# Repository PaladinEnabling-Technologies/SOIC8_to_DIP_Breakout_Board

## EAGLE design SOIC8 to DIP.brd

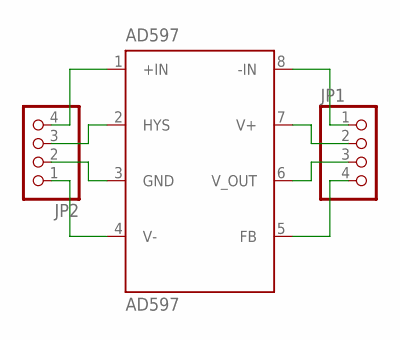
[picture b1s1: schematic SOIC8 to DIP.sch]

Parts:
AD597: AD597; SO8
JP1, JP2: PINHD-1X4; 1X04

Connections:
unnamed: AD597.1 (+IN), JP2.4
unnamed: AD597.2 (HYS), JP2.3
unnamed: AD597.3 (GND), JP2.2
unnamed: AD597.4 (V-), JP2.1
unnamed: AD597.6 (V_OUT), JP1.3
unnamed: AD597.7 (V+), JP1.2
unnamed: AD597.8 (-IN), JP1.1
unnamed: AD597.5 (FB), JP1.4

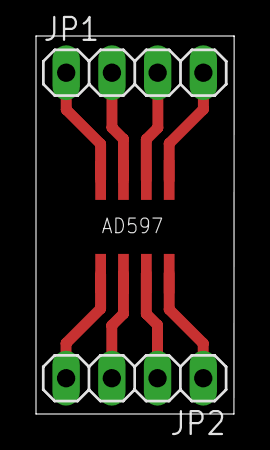
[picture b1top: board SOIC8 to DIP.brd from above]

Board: 2 copper layers, 11.0 x 21.0 mm, 3 parts (0 on the bottom side), 8 nets.

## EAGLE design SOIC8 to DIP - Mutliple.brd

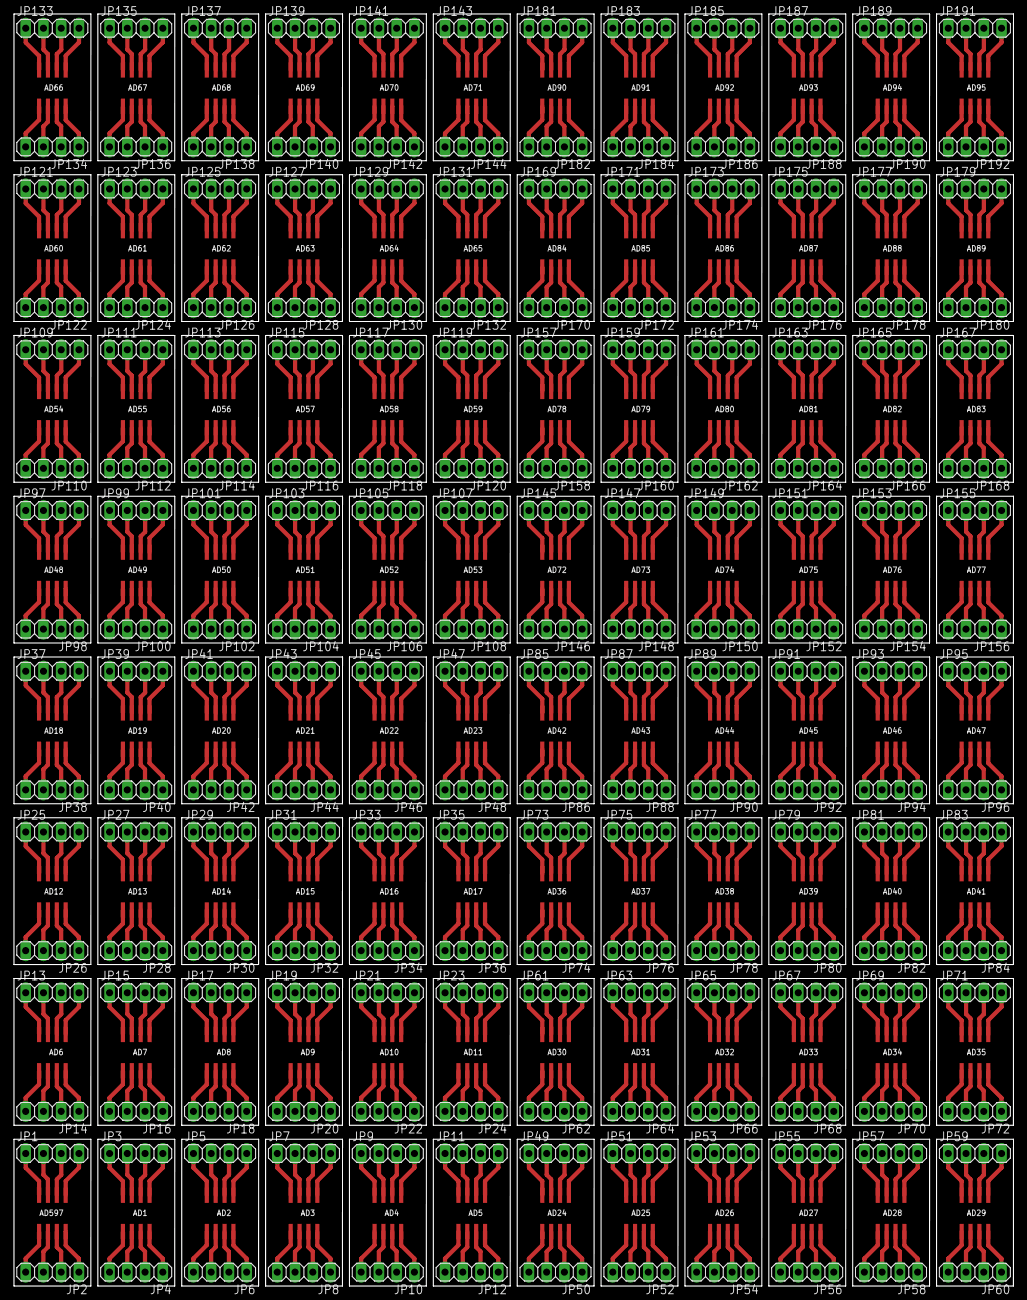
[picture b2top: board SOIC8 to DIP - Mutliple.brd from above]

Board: 2 copper layers, 143.0 x 182.0 mm, 288 parts (0 on the bottom side), 768 nets.

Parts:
AD1, AD2, AD3, AD4, AD5, AD6, AD7, AD8, AD9, AD10, AD11, AD12, AD13, AD14, AD15, AD16, AD17, AD18, AD19, AD20, AD21, AD22, AD23, AD24, AD25, AD26, AD27, AD28, AD29, AD30, AD31, AD32, AD33, AD34, AD35, AD36, AD37, AD38, AD39, AD40, AD41, AD42, AD43, AD44, AD45, AD46, AD47, AD48, AD49, AD50, AD51, AD52, AD53, AD54, AD55, AD56, AD57, AD58, AD59, AD60, AD61, AD62, AD63, AD64, AD65, AD66, AD67, AD68, AD69, AD70, AD71, AD72, AD73, AD74, AD75, AD76, AD77, AD78, AD79, AD80, AD81, AD82, AD83, AD84, AD85, AD86, AD87, AD88, AD89, AD90, AD91, AD92, AD93, AD94, AD95, AD597: AD597; SO8
JP1, JP2, JP3, JP4, JP5, JP6, JP7, JP8, JP9, JP10, JP11, JP12, JP13, JP14, JP15, JP16, JP17, JP18, JP19, JP20, JP21, JP22, JP23, JP24, JP25, JP26, JP27, JP28, JP29, JP30, JP31, JP32, JP33, JP34, JP35, JP36, JP37, JP38, JP39, JP40, JP41, JP42, JP43, JP44, JP45, JP46, JP47, JP48, JP49, JP50, JP51, JP52, JP53, JP54, JP55, JP56, JP57, JP58, JP59, JP60, JP61, JP62, JP63, JP64, JP65, JP66, JP67, JP68, JP69, JP70, JP71, JP72, JP73, JP74, JP75, JP76, JP77, JP78, JP79, JP80, JP81, JP82, JP83, JP84, JP85, JP86, JP87, JP88, JP89, JP90, JP91, JP92, JP93, JP94, JP95, JP96, JP97, JP98, JP99, JP100, JP101, JP102, JP103, JP104, JP105, JP106, JP107, JP108, JP109, JP110, JP111, JP112, JP113, JP114, JP115, JP116, JP117, JP118, JP119, JP120, JP121, JP122, JP123, JP124, JP125, JP126, JP127, JP128, JP129, JP130, JP131, JP132, JP133, JP134, JP135, JP136, JP137, JP138, JP139, JP140, JP141, JP142, JP143, JP144, JP145, JP146, JP147, JP148, JP149, JP150, JP151, JP152, JP153, JP154, JP155, JP156, JP157, JP158, JP159, JP160, JP161, JP162, JP163, JP164, JP165, JP166, JP167, JP168, JP169, JP170, JP171, JP172, JP173, JP174, JP175, JP176, JP177, JP178, JP179, JP180, JP181, JP182, JP183, JP184, JP185, JP186, JP187, JP188, JP189, JP190, JP191, JP192: 1X04

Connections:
unnamed: AD597.1, JP2.4
unnamed: AD1.1, JP4.4
unnamed: AD597.2, JP2.3
unnamed: AD597.3, JP2.2
unnamed: AD597.4, JP2.1
unnamed: AD1.2, JP4.3
unnamed: AD597.6, JP1.3
unnamed: AD1.3, JP4.2
unnamed: AD1.4, JP4.1
unnamed: AD1.6, JP3.3
unnamed: AD597.7, JP1.2
unnamed: AD597.8, JP1.1
unnamed: AD597.5, JP1.4
unnamed: AD1.7, JP3.2
unnamed: AD1.8, JP3.1
unnamed: AD1.5, JP3.4
unnamed: AD2.1, JP6.4
unnamed: AD2.2, JP6.3
unnamed: AD2.3, JP6.2
unnamed: AD2.4, JP6.1
unnamed: AD2.6, JP5.3
unnamed: AD2.7, JP5.2
unnamed: AD2.8, JP5.1
unnamed: AD2.5, JP5.4
unnamed: AD3.1, JP8.4
unnamed: AD3.2, JP8.3
unnamed: AD3.3, JP8.2
unnamed: AD3.4, JP8.1
unnamed: AD3.6, JP7.3
unnamed: AD3.7, JP7.2
unnamed: AD3.8, JP7.1
unnamed: AD3.5, JP7.4
unnamed: AD4.1, JP10.4
unnamed: AD4.2, JP10.3
unnamed: AD4.3, JP10.2
unnamed: AD4.4, JP10.1
unnamed: AD4.6, JP9.3
unnamed: AD4.7, JP9.2
unnamed: AD4.8, JP9.1
unnamed: AD4.5, JP9.4
unnamed: AD5.1, JP12.4
unnamed: AD5.2, JP12.3
unnamed: AD5.3, JP12.2
unnamed: AD5.4, JP12.1
unnamed: AD5.6, JP11.3
unnamed: AD5.7, JP11.2
unnamed: AD5.8, JP11.1
unnamed: AD5.5, JP11.4
unnamed: AD6.1, JP14.4
unnamed: AD6.2, JP14.3
unnamed: AD6.3, JP14.2
unnamed: AD6.4, JP14.1
unnamed: AD6.6, JP13.3
unnamed: AD6.7, JP13.2
unnamed: AD6.8, JP13.1
unnamed: AD6.5, JP13.4
unnamed: AD7.1, JP16.4
unnamed: AD7.2, JP16.3
unnamed: AD7.3, JP16.2
unnamed: AD7.4, JP16.1
unnamed: AD7.6, JP15.3
unnamed: AD7.7, JP15.2
unnamed: AD7.8, JP15.1
unnamed: AD7.5, JP15.4
unnamed: AD8.1, JP18.4
unnamed: AD8.2, JP18.3
unnamed: AD8.3, JP18.2
unnamed: AD8.4, JP18.1
unnamed: AD8.6, JP17.3
unnamed: AD8.7, JP17.2
unnamed: AD8.8, JP17.1
unnamed: AD8.5, JP17.4
unnamed: AD9.1, JP20.4
unnamed: AD9.2, JP20.3
unnamed: AD9.3, JP20.2
unnamed: AD9.4, JP20.1
unnamed: AD9.6, JP19.3
unnamed: AD9.7, JP19.2
unnamed: AD9.8, JP19.1
unnamed: AD9.5, JP19.4
unnamed: AD10.1, JP22.4
unnamed: AD10.2, JP22.3
unnamed: AD10.3, JP22.2
unnamed: AD10.4, JP22.1
unnamed: AD10.6, JP21.3
unnamed: AD10.7, JP21.2
unnamed: AD10.8, JP21.1
unnamed: AD10.5, JP21.4
unnamed: AD11.1, JP24.4
unnamed: AD11.2, JP24.3
unnamed: AD11.3, JP24.2
unnamed: AD11.4, JP24.1
unnamed: AD11.6, JP23.3
unnamed: AD11.7, JP23.2
unnamed: AD11.8, JP23.1
unnamed: AD11.5, JP23.4
unnamed: AD12.1, JP26.4
unnamed: AD12.2, JP26.3
unnamed: AD12.3, JP26.2
unnamed: AD12.4, JP26.1
unnamed: AD12.6, JP25.3
unnamed: AD12.7, JP25.2
unnamed: AD12.8, JP25.1
unnamed: AD12.5, JP25.4
unnamed: AD13.1, JP28.4
unnamed: AD13.2, JP28.3
unnamed: AD13.3, JP28.2
unnamed: AD13.4, JP28.1
unnamed: AD13.6, JP27.3
unnamed: AD13.7, JP27.2
unnamed: AD13.8, JP27.1
unnamed: AD13.5, JP27.4
unnamed: AD14.1, JP30.4
unnamed: AD14.2, JP30.3
unnamed: AD14.3, JP30.2
unnamed: AD14.4, JP30.1
unnamed: AD14.6, JP29.3
unnamed: AD14.7, JP29.2
unnamed: AD14.8, JP29.1
unnamed: AD14.5, JP29.4
unnamed: AD15.1, JP32.4
unnamed: AD15.2, JP32.3
unnamed: AD15.3, JP32.2
unnamed: AD15.4, JP32.1
unnamed: AD15.6, JP31.3
unnamed: AD15.7, JP31.2
unnamed: AD15.8, JP31.1
unnamed: AD15.5, JP31.4
unnamed: AD16.1, JP34.4
unnamed: AD16.2, JP34.3
unnamed: AD16.3, JP34.2
unnamed: AD16.4, JP34.1
unnamed: AD16.6, JP33.3
unnamed: AD16.7, JP33.2
unnamed: AD16.8, JP33.1
unnamed: AD16.5, JP33.4
unnamed: AD17.1, JP36.4
unnamed: AD17.2, JP36.3
unnamed: AD17.3, JP36.2
unnamed: AD17.4, JP36.1
unnamed: AD17.6, JP35.3
unnamed: AD17.7, JP35.2
unnamed: AD17.8, JP35.1
unnamed: AD17.5, JP35.4
unnamed: AD18.1, JP38.4
unnamed: AD18.2, JP38.3
unnamed: AD18.3, JP38.2
unnamed: AD18.4, JP38.1
unnamed: AD18.6, JP37.3
unnamed: AD18.7, JP37.2
unnamed: AD18.8, JP37.1
unnamed: AD18.5, JP37.4
unnamed: AD19.1, JP40.4
unnamed: AD19.2, JP40.3
unnamed: AD19.3, JP40.2
unnamed: AD19.4, JP40.1
unnamed: AD19.6, JP39.3
unnamed: AD19.7, JP39.2
unnamed: AD19.8, JP39.1
unnamed: AD19.5, JP39.4
unnamed: AD20.1, JP42.4
unnamed: AD20.2, JP42.3
unnamed: AD20.3, JP42.2
unnamed: AD20.4, JP42.1
unnamed: AD20.6, JP41.3
unnamed: AD20.7, JP41.2
unnamed: AD20.8, JP41.1
unnamed: AD20.5, JP41.4
unnamed: AD21.1, JP44.4
unnamed: AD21.2, JP44.3
unnamed: AD21.3, JP44.2
unnamed: AD21.4, JP44.1
unnamed: AD21.6, JP43.3
unnamed: AD21.7, JP43.2
unnamed: AD21.8, JP43.1
unnamed: AD21.5, JP43.4
unnamed: AD22.1, JP46.4
unnamed: AD22.2, JP46.3
unnamed: AD22.3, JP46.2
unnamed: AD22.4, JP46.1
unnamed: AD22.6, JP45.3
unnamed: AD22.7, JP45.2
unnamed: AD22.8, JP45.1
unnamed: AD22.5, JP45.4
unnamed: AD23.1, JP48.4
unnamed: AD23.2, JP48.3
unnamed: AD23.3, JP48.2
unnamed: AD23.4, JP48.1
unnamed: AD23.6, JP47.3
unnamed: AD23.7, JP47.2
unnamed: AD23.8, JP47.1
unnamed: AD23.5, JP47.4
unnamed: AD24.1, JP50.4
unnamed: AD24.2, JP50.3
unnamed: AD24.3, JP50.2
unnamed: AD24.4, JP50.1
unnamed: AD24.6, JP49.3
unnamed: AD24.7, JP49.2
unnamed: AD24.8, JP49.1
unnamed: AD24.5, JP49.4
unnamed: AD25.1, JP52.4
unnamed: AD25.2, JP52.3
unnamed: AD25.3, JP52.2
unnamed: AD25.4, JP52.1
unnamed: AD25.6, JP51.3
unnamed: AD25.7, JP51.2
unnamed: AD25.8, JP51.1
unnamed: AD25.5, JP51.4
unnamed: AD26.1, JP54.4
unnamed: AD26.2, JP54.3
unnamed: AD26.3, JP54.2
unnamed: AD26.4, JP54.1
unnamed: AD26.6, JP53.3
unnamed: AD26.7, JP53.2
unnamed: AD26.8, JP53.1
unnamed: AD26.5, JP53.4
unnamed: AD27.1, JP56.4
unnamed: AD27.2, JP56.3
unnamed: AD27.3, JP56.2
unnamed: AD27.4, JP56.1
unnamed: AD27.6, JP55.3
unnamed: AD27.7, JP55.2
unnamed: AD27.8, JP55.1
unnamed: AD27.5, JP55.4
unnamed: AD28.1, JP58.4
unnamed: AD28.2, JP58.3
unnamed: AD28.3, JP58.2
unnamed: AD28.4, JP58.1
unnamed: AD28.6, JP57.3
unnamed: AD28.7, JP57.2
unnamed: AD28.8, JP57.1
unnamed: AD28.5, JP57.4
unnamed: AD29.1, JP60.4
unnamed: AD29.2, JP60.3
unnamed: AD29.3, JP60.2
unnamed: AD29.4, JP60.1
unnamed: AD29.6, JP59.3
unnamed: AD29.7, JP59.2
unnamed: AD29.8, JP59.1
unnamed: AD29.5, JP59.4
unnamed: AD30.1, JP62.4
unnamed: AD30.2, JP62.3
unnamed: AD30.3, JP62.2
unnamed: AD30.4, JP62.1
unnamed: AD30.6, JP61.3
unnamed: AD30.7, JP61.2
unnamed: AD30.8, JP61.1
unnamed: AD30.5, JP61.4
unnamed: AD31.1, JP64.4
unnamed: AD31.2, JP64.3
unnamed: AD31.3, JP64.2
unnamed: AD31.4, JP64.1
unnamed: AD31.6, JP63.3
unnamed: AD31.7, JP63.2
unnamed: AD31.8, JP63.1
unnamed: AD31.5, JP63.4
unnamed: AD32.1, JP66.4
unnamed: AD32.2, JP66.3
unnamed: AD32.3, JP66.2
unnamed: AD32.4, JP66.1
unnamed: AD32.6, JP65.3
unnamed: AD32.7, JP65.2
unnamed: AD32.8, JP65.1
unnamed: AD32.5, JP65.4
unnamed: AD33.1, JP68.4
unnamed: AD33.2, JP68.3
unnamed: AD33.3, JP68.2
unnamed: AD33.4, JP68.1
unnamed: AD33.6, JP67.3
unnamed: AD33.7, JP67.2
unnamed: AD33.8, JP67.1
unnamed: AD33.5, JP67.4
unnamed: AD34.1, JP70.4
unnamed: AD34.2, JP70.3
unnamed: AD34.3, JP70.2
unnamed: AD34.4, JP70.1
unnamed: AD34.6, JP69.3
unnamed: AD34.7, JP69.2
unnamed: AD34.8, JP69.1
unnamed: AD34.5, JP69.4
unnamed: AD35.1, JP72.4
unnamed: AD35.2, JP72.3
unnamed: AD35.3, JP72.2
unnamed: AD35.4, JP72.1
unnamed: AD35.6, JP71.3
unnamed: AD35.7, JP71.2
unnamed: AD35.8, JP71.1
unnamed: AD35.5, JP71.4
unnamed: AD36.1, JP74.4
unnamed: AD36.2, JP74.3
unnamed: AD36.3, JP74.2
unnamed: AD36.4, JP74.1
unnamed: AD36.6, JP73.3
unnamed: AD36.7, JP73.2
unnamed: AD36.8, JP73.1
unnamed: AD36.5, JP73.4
unnamed: AD37.1, JP76.4
unnamed: AD37.2, JP76.3
unnamed: AD37.3, JP76.2
unnamed: AD37.4, JP76.1
unnamed: AD37.6, JP75.3
unnamed: AD37.7, JP75.2
unnamed: AD37.8, JP75.1
unnamed: AD37.5, JP75.4
unnamed: AD38.1, JP78.4
unnamed: AD38.2, JP78.3
unnamed: AD38.3, JP78.2
unnamed: AD38.4, JP78.1
unnamed: AD38.6, JP77.3
unnamed: AD38.7, JP77.2
unnamed: AD38.8, JP77.1
unnamed: AD38.5, JP77.4
unnamed: AD39.1, JP80.4
unnamed: AD39.2, JP80.3
unnamed: AD39.3, JP80.2
unnamed: AD39.4, JP80.1
unnamed: AD39.6, JP79.3
unnamed: AD39.7, JP79.2
unnamed: AD39.8, JP79.1
unnamed: AD39.5, JP79.4
unnamed: AD40.1, JP82.4
unnamed: AD40.2, JP82.3
unnamed: AD40.3, JP82.2
unnamed: AD40.4, JP82.1
unnamed: AD40.6, JP81.3
unnamed: AD40.7, JP81.2
unnamed: AD40.8, JP81.1
unnamed: AD40.5, JP81.4
unnamed: AD41.1, JP84.4
unnamed: AD41.2, JP84.3
unnamed: AD41.3, JP84.2
unnamed: AD41.4, JP84.1
unnamed: AD41.6, JP83.3
unnamed: AD41.7, JP83.2
unnamed: AD41.8, JP83.1
unnamed: AD41.5, JP83.4
unnamed: AD42.1, JP86.4
unnamed: AD42.2, JP86.3
unnamed: AD42.3, JP86.2
unnamed: AD42.4, JP86.1
unnamed: AD42.6, JP85.3
unnamed: AD42.7, JP85.2
unnamed: AD42.8, JP85.1
unnamed: AD42.5, JP85.4
unnamed: AD43.1, JP88.4
unnamed: AD43.2, JP88.3
unnamed: AD43.3, JP88.2
unnamed: AD43.4, JP88.1
unnamed: AD43.6, JP87.3
unnamed: AD43.7, JP87.2
unnamed: AD43.8, JP87.1
unnamed: AD43.5, JP87.4
unnamed: AD44.1, JP90.4
unnamed: AD44.2, JP90.3
unnamed: AD44.3, JP90.2
unnamed: AD44.4, JP90.1
unnamed: AD44.6, JP89.3
unnamed: AD44.7, JP89.2
unnamed: AD44.8, JP89.1
unnamed: AD44.5, JP89.4
unnamed: AD45.1, JP92.4
unnamed: AD45.2, JP92.3
unnamed: AD45.3, JP92.2
unnamed: AD45.4, JP92.1
unnamed: AD45.6, JP91.3
unnamed: AD45.7, JP91.2
unnamed: AD45.8, JP91.1
unnamed: AD45.5, JP91.4
unnamed: AD46.1, JP94.4
unnamed: AD46.2, JP94.3
unnamed: AD46.3, JP94.2
unnamed: AD46.4, JP94.1
unnamed: AD46.6, JP93.3
unnamed: AD46.7, JP93.2
unnamed: AD46.8, JP93.1
unnamed: AD46.5, JP93.4
unnamed: AD47.1, JP96.4
unnamed: AD47.2, JP96.3
unnamed: AD47.3, JP96.2
unnamed: AD47.4, JP96.1
unnamed: AD47.6, JP95.3
unnamed: AD47.7, JP95.2
unnamed: AD47.8, JP95.1
unnamed: AD47.5, JP95.4
unnamed: AD48.1, JP98.4
unnamed: AD48.2, JP98.3
unnamed: AD48.3, JP98.2
unnamed: AD48.4, JP98.1
unnamed: AD48.6, JP97.3
unnamed: AD48.7, JP97.2
unnamed: AD48.8, JP97.1
unnamed: AD48.5, JP97.4
unnamed: AD49.1, JP100.4
unnamed: AD49.2, JP100.3
unnamed: AD49.3, JP100.2
unnamed: AD49.4, JP100.1
unnamed: AD49.6, JP99.3
unnamed: AD49.7, JP99.2
unnamed: AD49.8, JP99.1
unnamed: AD49.5, JP99.4
unnamed: AD50.1, JP102.4
unnamed: AD50.2, JP102.3
unnamed: AD50.3, JP102.2
unnamed: AD50.4, JP102.1
unnamed: AD50.6, JP101.3
unnamed: AD50.7, JP101.2
unnamed: AD50.8, JP101.1
unnamed: AD50.5, JP101.4
unnamed: AD51.1, JP104.4
unnamed: AD51.2, JP104.3
unnamed: AD51.3, JP104.2
unnamed: AD51.4, JP104.1
unnamed: AD51.6, JP103.3
unnamed: AD51.7, JP103.2
unnamed: AD51.8, JP103.1
unnamed: AD51.5, JP103.4
unnamed: AD52.1, JP106.4
unnamed: AD52.2, JP106.3
unnamed: AD52.3, JP106.2
unnamed: AD52.4, JP106.1
unnamed: AD52.6, JP105.3
unnamed: AD52.7, JP105.2
unnamed: AD52.8, JP105.1
unnamed: AD52.5, JP105.4
unnamed: AD53.1, JP108.4
unnamed: AD53.2, JP108.3
unnamed: AD53.3, JP108.2
unnamed: AD53.4, JP108.1
unnamed: AD53.6, JP107.3
unnamed: AD53.7, JP107.2
unnamed: AD53.8, JP107.1
unnamed: AD53.5, JP107.4
unnamed: AD54.1, JP110.4
unnamed: AD54.2, JP110.3
unnamed: AD54.3, JP110.2
unnamed: AD54.4, JP110.1
unnamed: AD54.6, JP109.3
unnamed: AD54.7, JP109.2
unnamed: AD54.8, JP109.1
unnamed: AD54.5, JP109.4
unnamed: AD55.1, JP112.4
unnamed: AD55.2, JP112.3
unnamed: AD55.3, JP112.2
unnamed: AD55.4, JP112.1
unnamed: AD55.6, JP111.3
unnamed: AD55.7, JP111.2
unnamed: AD55.8, JP111.1
unnamed: AD55.5, JP111.4
unnamed: AD56.1, JP114.4
unnamed: AD56.2, JP114.3
unnamed: AD56.3, JP114.2
unnamed: AD56.4, JP114.1
unnamed: AD56.6, JP113.3
unnamed: AD56.7, JP113.2
unnamed: AD56.8, JP113.1
unnamed: AD56.5, JP113.4
unnamed: AD57.1, JP116.4
unnamed: AD57.2, JP116.3
unnamed: AD57.3, JP116.2
unnamed: AD57.4, JP116.1
unnamed: AD57.6, JP115.3
unnamed: AD57.7, JP115.2
unnamed: AD57.8, JP115.1
unnamed: AD57.5, JP115.4
unnamed: AD58.1, JP118.4
unnamed: AD58.2, JP118.3
unnamed: AD58.3, JP118.2
unnamed: AD58.4, JP118.1
unnamed: AD58.6, JP117.3
unnamed: AD58.7, JP117.2
unnamed: AD58.8, JP117.1
unnamed: AD58.5, JP117.4
unnamed: AD59.1, JP120.4
unnamed: AD59.2, JP120.3
unnamed: AD59.3, JP120.2
unnamed: AD59.4, JP120.1
unnamed: AD59.6, JP119.3
unnamed: AD59.7, JP119.2
unnamed: AD59.8, JP119.1
unnamed: AD59.5, JP119.4
unnamed: AD60.1, JP122.4
unnamed: AD60.2, JP122.3
unnamed: AD60.3, JP122.2
unnamed: AD60.4, JP122.1
unnamed: AD60.6, JP121.3
unnamed: AD60.7, JP121.2
unnamed: AD60.8, JP121.1
unnamed: AD60.5, JP121.4
unnamed: AD61.1, JP124.4
unnamed: AD61.2, JP124.3
unnamed: AD61.3, JP124.2
unnamed: AD61.4, JP124.1
unnamed: AD61.6, JP123.3
unnamed: AD61.7, JP123.2
unnamed: AD61.8, JP123.1
unnamed: AD61.5, JP123.4
unnamed: AD62.1, JP126.4
unnamed: AD62.2, JP126.3
unnamed: AD62.3, JP126.2
unnamed: AD62.4, JP126.1
unnamed: AD62.6, JP125.3
unnamed: AD62.7, JP125.2
unnamed: AD62.8, JP125.1
unnamed: AD62.5, JP125.4
unnamed: AD63.1, JP128.4
unnamed: AD63.2, JP128.3
unnamed: AD63.3, JP128.2
unnamed: AD63.4, JP128.1
unnamed: AD63.6, JP127.3
unnamed: AD63.7, JP127.2
unnamed: AD63.8, JP127.1
unnamed: AD63.5, JP127.4
unnamed: AD64.1, JP130.4
unnamed: AD64.2, JP130.3
unnamed: AD64.3, JP130.2
unnamed: AD64.4, JP130.1
unnamed: AD64.6, JP129.3
unnamed: AD64.7, JP129.2
unnamed: AD64.8, JP129.1
unnamed: AD64.5, JP129.4
unnamed: AD65.1, JP132.4
unnamed: AD65.2, JP132.3
unnamed: AD65.3, JP132.2
unnamed: AD65.4, JP132.1
unnamed: AD65.6, JP131.3
unnamed: AD65.7, JP131.2
unnamed: AD65.8, JP131.1
unnamed: AD65.5, JP131.4
unnamed: AD66.1, JP134.4
unnamed: AD66.2, JP134.3
unnamed: AD66.3, JP134.2
unnamed: AD66.4, JP134.1
unnamed: AD66.6, JP133.3
unnamed: AD66.7, JP133.2
unnamed: AD66.8, JP133.1
unnamed: AD66.5, JP133.4
unnamed: AD67.1, JP136.4
unnamed: AD67.2, JP136.3
unnamed: AD67.3, JP136.2
unnamed: AD67.4, JP136.1
unnamed: AD67.6, JP135.3
unnamed: AD67.7, JP135.2
unnamed: AD67.8, JP135.1
unnamed: AD67.5, JP135.4
unnamed: AD68.1, JP138.4
unnamed: AD68.2, JP138.3
unnamed: AD68.3, JP138.2
unnamed: AD68.4, JP138.1
unnamed: AD68.6, JP137.3
unnamed: AD68.7, JP137.2
unnamed: AD68.8, JP137.1
unnamed: AD68.5, JP137.4
unnamed: AD69.1, JP140.4
unnamed: AD69.2, JP140.3
unnamed: AD69.3, JP140.2
unnamed: AD69.4, JP140.1
unnamed: AD69.6, JP139.3
unnamed: AD69.7, JP139.2
unnamed: AD69.8, JP139.1
unnamed: AD69.5, JP139.4
unnamed: AD70.1, JP142.4
unnamed: AD70.2, JP142.3
unnamed: AD70.3, JP142.2
unnamed: AD70.4, JP142.1
unnamed: AD70.6, JP141.3
unnamed: AD70.7, JP141.2
unnamed: AD70.8, JP141.1
unnamed: AD70.5, JP141.4
unnamed: AD71.1, JP144.4
unnamed: AD71.2, JP144.3
unnamed: AD71.3, JP144.2
unnamed: AD71.4, JP144.1
unnamed: AD71.6, JP143.3
unnamed: AD71.7, JP143.2
unnamed: AD71.8, JP143.1
unnamed: AD71.5, JP143.4
unnamed: AD72.1, JP146.4
unnamed: AD72.2, JP146.3
unnamed: AD72.3, JP146.2
unnamed: AD72.4, JP146.1
unnamed: AD72.6, JP145.3
unnamed: AD72.7, JP145.2
unnamed: AD72.8, JP145.1
unnamed: AD72.5, JP145.4
unnamed: AD73.1, JP148.4
unnamed: AD73.2, JP148.3
unnamed: AD73.3, JP148.2
unnamed: AD73.4, JP148.1
unnamed: AD73.6, JP147.3
unnamed: AD73.7, JP147.2
unnamed: AD73.8, JP147.1
unnamed: AD73.5, JP147.4
unnamed: AD74.1, JP150.4
unnamed: AD74.2, JP150.3
unnamed: AD74.3, JP150.2
unnamed: AD74.4, JP150.1
unnamed: AD74.6, JP149.3
unnamed: AD74.7, JP149.2
unnamed: AD74.8, JP149.1
unnamed: AD74.5, JP149.4
unnamed: AD75.1, JP152.4
unnamed: AD75.2, JP152.3
unnamed: AD75.3, JP152.2
unnamed: AD75.4, JP152.1
unnamed: AD75.6, JP151.3
unnamed: AD75.7, JP151.2
unnamed: AD75.8, JP151.1
unnamed: AD75.5, JP151.4
unnamed: AD76.1, JP154.4
unnamed: AD76.2, JP154.3
unnamed: AD76.3, JP154.2
unnamed: AD76.4, JP154.1
unnamed: AD76.6, JP153.3
unnamed: AD76.7, JP153.2
unnamed: AD76.8, JP153.1
unnamed: AD76.5, JP153.4
unnamed: AD77.1, JP156.4
unnamed: AD77.2, JP156.3
unnamed: AD77.3, JP156.2
unnamed: AD77.4, JP156.1
unnamed: AD77.6, JP155.3
unnamed: AD77.7, JP155.2
unnamed: AD77.8, JP155.1
unnamed: AD77.5, JP155.4
unnamed: AD78.1, JP158.4
unnamed: AD78.2, JP158.3
unnamed: AD78.3, JP158.2
unnamed: AD78.4, JP158.1
unnamed: AD78.6, JP157.3
unnamed: AD78.7, JP157.2
unnamed: AD78.8, JP157.1
unnamed: AD78.5, JP157.4
unnamed: AD79.1, JP160.4
unnamed: AD79.2, JP160.3
unnamed: AD79.3, JP160.2
unnamed: AD79.4, JP160.1
unnamed: AD79.6, JP159.3
unnamed: AD79.7, JP159.2
unnamed: AD79.8, JP159.1
unnamed: AD79.5, JP159.4
unnamed: AD80.1, JP162.4
unnamed: AD80.2, JP162.3
unnamed: AD80.3, JP162.2
unnamed: AD80.4, JP162.1
unnamed: AD80.6, JP161.3
unnamed: AD80.7, JP161.2
unnamed: AD80.8, JP161.1
unnamed: AD80.5, JP161.4
unnamed: AD81.1, JP164.4
unnamed: AD81.2, JP164.3
unnamed: AD81.3, JP164.2
unnamed: AD81.4, JP164.1
unnamed: AD81.6, JP163.3
unnamed: AD81.7, JP163.2
unnamed: AD81.8, JP163.1
unnamed: AD81.5, JP163.4
unnamed: AD82.1, JP166.4
unnamed: AD82.2, JP166.3
unnamed: AD82.3, JP166.2
unnamed: AD82.4, JP166.1
unnamed: AD82.6, JP165.3
unnamed: AD82.7, JP165.2
unnamed: AD82.8, JP165.1
unnamed: AD82.5, JP165.4
unnamed: AD83.1, JP168.4
unnamed: AD83.2, JP168.3
unnamed: AD83.3, JP168.2
unnamed: AD83.4, JP168.1
unnamed: AD83.6, JP167.3
unnamed: AD83.7, JP167.2
unnamed: AD83.8, JP167.1
unnamed: AD83.5, JP167.4
unnamed: AD84.1, JP170.4
unnamed: AD84.2, JP170.3
unnamed: AD84.3, JP170.2
unnamed: AD84.4, JP170.1
unnamed: AD84.6, JP169.3
unnamed: AD84.7, JP169.2
unnamed: AD84.8, JP169.1
unnamed: AD84.5, JP169.4
unnamed: AD85.1, JP172.4
unnamed: AD85.2, JP172.3
unnamed: AD85.3, JP172.2
unnamed: AD85.4, JP172.1
unnamed: AD85.6, JP171.3
unnamed: AD85.7, JP171.2
unnamed: AD85.8, JP171.1
unnamed: AD85.5, JP171.4
unnamed: AD86.1, JP174.4
unnamed: AD86.2, JP174.3
unnamed: AD86.3, JP174.2
unnamed: AD86.4, JP174.1
unnamed: AD86.6, JP173.3
unnamed: AD86.7, JP173.2
unnamed: AD86.8, JP173.1
unnamed: AD86.5, JP173.4
unnamed: AD87.1, JP176.4
unnamed: AD87.2, JP176.3
unnamed: AD87.3, JP176.2
unnamed: AD87.4, JP176.1
unnamed: AD87.6, JP175.3
unnamed: AD87.7, JP175.2
unnamed: AD87.8, JP175.1
unnamed: AD87.5, JP175.4
unnamed: AD88.1, JP178.4
unnamed: AD88.2, JP178.3
unnamed: AD88.3, JP178.2
unnamed: AD88.4, JP178.1
unnamed: AD88.6, JP177.3
unnamed: AD88.7, JP177.2
unnamed: AD88.8, JP177.1
unnamed: AD88.5, JP177.4
unnamed: AD89.1, JP180.4
unnamed: AD89.2, JP180.3
unnamed: AD89.3, JP180.2
unnamed: AD89.4, JP180.1
unnamed: AD89.6, JP179.3
unnamed: AD89.7, JP179.2
unnamed: AD89.8, JP179.1
unnamed: AD89.5, JP179.4
unnamed: AD90.1, JP182.4
unnamed: AD90.2, JP182.3
unnamed: AD90.3, JP182.2
unnamed: AD90.4, JP182.1
unnamed: AD90.6, JP181.3
unnamed: AD90.7, JP181.2
unnamed: AD90.8, JP181.1
unnamed: AD90.5, JP181.4
unnamed: AD91.1, JP184.4
unnamed: AD91.2, JP184.3
unnamed: AD91.3, JP184.2
unnamed: AD91.4, JP184.1
unnamed: AD91.6, JP183.3
unnamed: AD91.7, JP183.2
unnamed: AD91.8, JP183.1
unnamed: AD91.5, JP183.4
unnamed: AD92.1, JP186.4
unnamed: AD92.2, JP186.3
unnamed: AD92.3, JP186.2
unnamed: AD92.4, JP186.1
unnamed: AD92.6, JP185.3
unnamed: AD92.7, JP185.2
unnamed: AD92.8, JP185.1
unnamed: AD92.5, JP185.4
unnamed: AD93.1, JP188.4
unnamed: AD93.2, JP188.3
unnamed: AD93.3, JP188.2
unnamed: AD93.4, JP188.1
unnamed: AD93.6, JP187.3
unnamed: AD93.7, JP187.2
unnamed: AD93.8, JP187.1
unnamed: AD93.5, JP187.4
unnamed: AD94.1, JP190.4
unnamed: AD94.2, JP190.3
unnamed: AD94.3, JP190.2
unnamed: AD94.4, JP190.1
unnamed: AD94.6, JP189.3
unnamed: AD94.7, JP189.2
unnamed: AD94.8, JP189.1
unnamed: AD94.5, JP189.4
unnamed: AD95.1, JP192.4
unnamed: AD95.2, JP192.3
unnamed: AD95.3, JP192.2
unnamed: AD95.4, JP192.1
unnamed: AD95.6, JP191.3
unnamed: AD95.7, JP191.2
unnamed: AD95.8, JP191.1
unnamed: AD95.5, JP191.4

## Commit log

2014-07-30 Soic-Dip Breakout Board
    Just a little breakout board to put your SOIC 8 package on a DIP
    breakout board for prototyping purposes;
